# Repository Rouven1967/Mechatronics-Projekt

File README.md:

# Mechatronics-Projekt
Messtechnik für den Arbeitsschutz

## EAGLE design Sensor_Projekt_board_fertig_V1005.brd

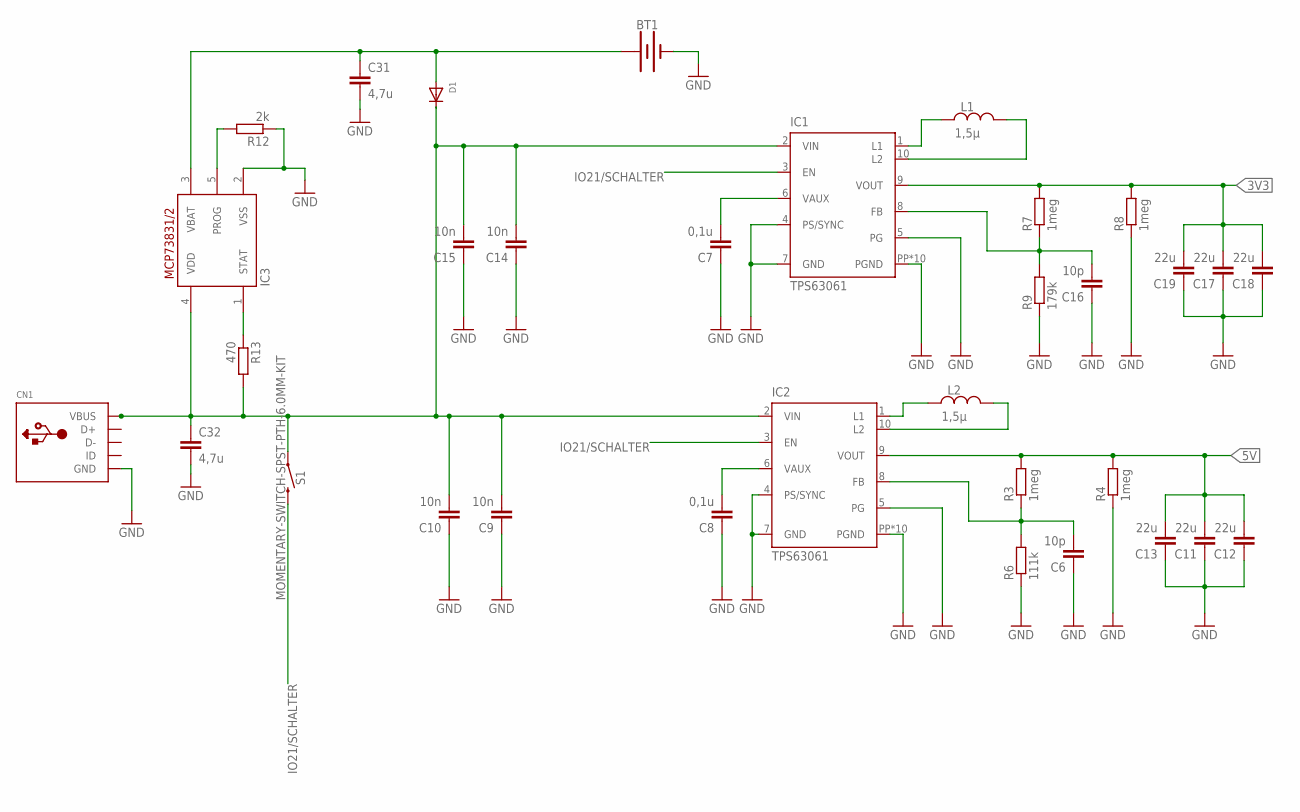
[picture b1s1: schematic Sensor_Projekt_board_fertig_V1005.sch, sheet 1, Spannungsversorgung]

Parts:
BT1: BATTERY-18650; BATTERY_18650-HOLDER
C6, C16: 10p; C0603
C7, C8: 0,1u; C0603
C9, C10, C14, C15: 10n; C0603
C11, C12, C13, C17, C18, C19: 22u; C0603
C31, C32: 4,7u; C0603
CN1: USBTHM; USB-MINIB-THM
D1: DIODE_SOD-123FL; SOD-123FL
IC1, IC2: TPS63061; DSC-S-PWSON-N10
IC3: MCP73831/OT; SOT23-5L
L1, L2: 1,5µ; INDC2520X120N
R3, R4, R7, R8: 1meg; R0603
R6: 111k; R0603
R9: 179k; R0603
R12: 2k; R0603
R13: 470; R0603
S1: MOMENTARY-SWITCH-SPST-PTH-6.0MM-KIT; TACTILE_SWITCH_PTH_6.0MM_KIT

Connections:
3V3: C17.2, C18.2, C19.2, IC1.9 (VOUT), R7.2, R8.2; also elsewhere on the board
5V: C11.2, C12.2, C13.2, IC2.9 (VOUT), R3.2, R4.2; also elsewhere on the board
GND: BT1.GND@1 (-), C6.1, C7.1, C8.1, C9.1, C10.1, C11.1, C12.1, C13.1, C14.1, C15.1, C16.1, C17.1, C18.1, C19.1, C31.2, C32.2, CN1.GND, IC1.4 (PS/SYNC), IC1.7 (GND), IC1.PP (PGND), IC1.PP@1 (PGND), IC1.PP@2 (PGND), IC1.PP@3 (PGND), IC1.PP@4 (PGND), IC1.PP@5 (PGND), IC1.PP@7 (PGND), IC1.PP@8 (PGND), IC1.PP@9 (PGND), IC1.PP@10 (PGND), IC2.4 (PS/SYNC), IC2.5 (PG), IC2.7 (GND), IC2.PP (PGND), IC2.PP@1 (PGND), IC2.PP@2 (PGND), IC2.PP@3 (PGND), IC2.PP@4 (PGND), IC2.PP@5 (PGND), IC2.PP@7 (PGND), IC2.PP@8 (PGND), IC2.PP@9 (PGND), IC2.PP@10 (PGND), IC3.2 (VSS), R4.1, R6.1, R8.1, R9.1, R12.1; also elsewhere on the board
IO21/SCHALTER: IC1.3 (EN), IC2.3 (EN), S1.3 (2); also elsewhere on the board
unnamed: IC3.5 (PROG), R12.2
unnamed: BT1.PWR@1 (+), C31.1, D1.A, IC3.3 (VBAT)
unnamed: C8.2, IC2.6 (VAUX)
unnamed: C7.2, IC1.6 (VAUX)
unnamed: C9.2, C10.2, C14.2, C15.2, C32.1, CN1.VBUS, D1.C, IC1.2 (VIN), IC2.2 (VIN), IC3.4 (VDD), R13.2, S1.1
unnamed: IC2.10 (L2), L2.2
unnamed: IC1.1 (L1), L1.1
unnamed: IC1.10 (L2), L1.2
unnamed: C6.2, IC2.8 (FB), R3.1, R6.2
unnamed: C16.2, IC1.8 (FB), R7.1, R9.2
unnamed: IC2.1 (L1), L2.1
unnamed: IC3.1 (STAT), R13.1

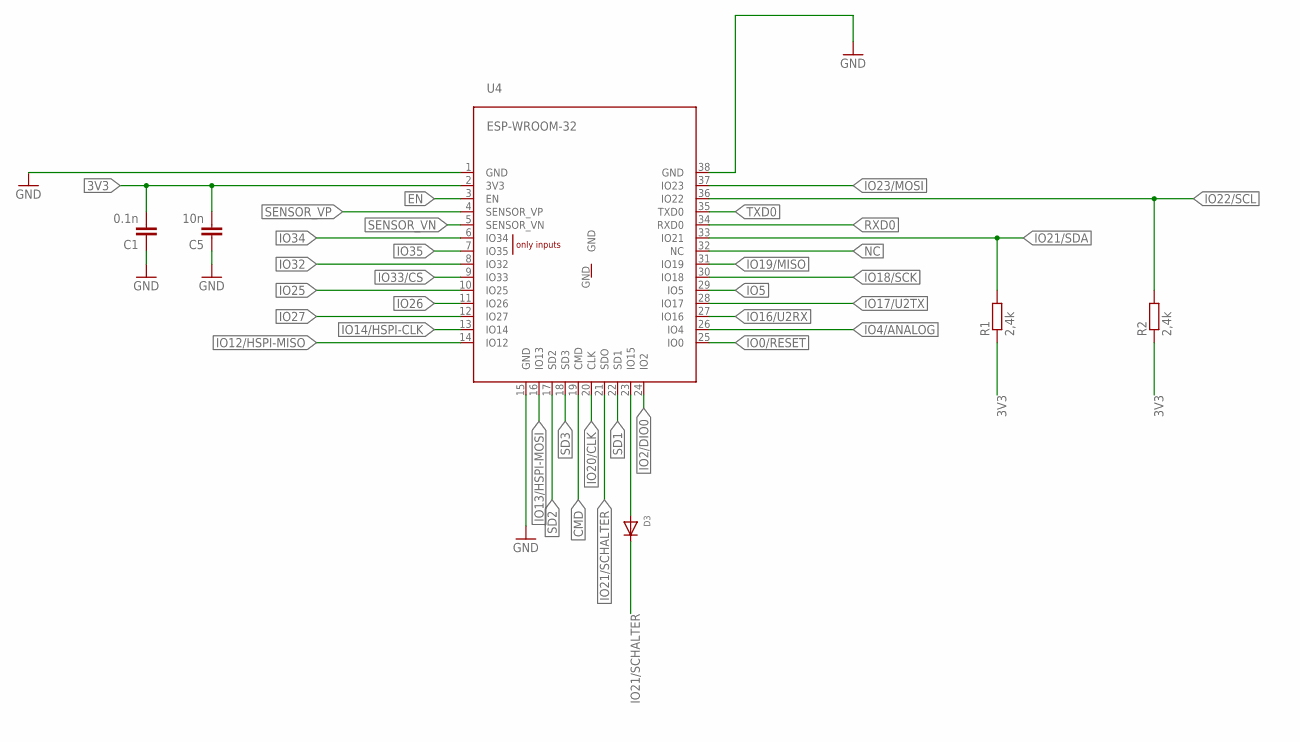
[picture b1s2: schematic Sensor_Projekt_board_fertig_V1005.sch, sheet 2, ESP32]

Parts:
C1: 0.1n; C0603
C5: 10n; C0603
D3: DIODE_SOD-123FL; SOD-123FL
R1, R2: 2,4k; R0603
U4: ESP-WROOM-32

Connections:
3V3: C1.2, C5.2, R1.1, R2.1, U4.2 (3V3); also elsewhere on the board
CMD: U4.19 (CMD)
EN: U4.3 (EN)
GND: C1.1, C5.1, U4.1 (GND), U4.15 (GND), U4.38 (GND); also elsewhere on the board
IO0/RESET: U4.25 (IO0); also elsewhere on the board
IO2/DIO0: U4.24 (IO2); also elsewhere on the board
IO4/ANALOG: U4.26 (IO4); also elsewhere on the board
IO5: U4.29 (IO5); also elsewhere on the board
IO12/HSPI-MISO: U4.14 (IO12); also elsewhere on the board
IO13/HSPI-MOSI: U4.16 (IO13); also elsewhere on the board
IO14/HSPI-CLK: U4.13 (IO14); also elsewhere on the board
IO15/VCC_ENABLE: D3.A, U4.23 (IO15)
IO16/U2RX: U4.27 (IO16); also elsewhere on the board
IO17/U2TX: U4.28 (IO17)
IO18/SCK: U4.30 (IO18); also elsewhere on the board
IO19/MISO: U4.31 (IO19); also elsewhere on the board
IO20/CLK: U4.20 (CLK)
IO21/SCHALTER: D3.C, U4.21 (SDO); also elsewhere on the board
IO21/SDA: R1.2, U4.33 (IO21); also elsewhere on the board
IO22/SCL: R2.2, U4.36 (IO22); also elsewhere on the board
IO23/MOSI: U4.37 (IO23); also elsewhere on the board
IO25: U4.10 (IO25)
IO26: U4.11 (IO26)
IO27: U4.12 (IO27)
IO32: U4.8 (IO32)
IO33/CS: U4.9 (IO33); also elsewhere on the board
IO34: U4.6 (IO34)
IO35: U4.7 (IO35)
NC: U4.32 (NC)
RXD0: U4.34 (RXD0); also elsewhere on the board
SD1: U4.22 (SD1)
SD2: U4.17 (SD2)
SD3: U4.18 (SD3)
SENSOR_VN: U4.5 (SENSOR_VN)
SENSOR_VP: U4.4 (SENSOR_VP)
TXD0: U4.35 (TXD0); also elsewhere on the board

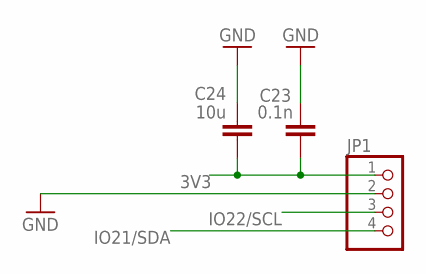
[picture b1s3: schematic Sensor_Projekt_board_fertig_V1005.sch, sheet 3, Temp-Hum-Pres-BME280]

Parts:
C23: 0.1n; C0603
C24: 10u; C0603
JP1: PINHD-1X4; 1X04

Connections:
3V3: C23.1, C24.1, JP1.1; also elsewhere on the board
GND: C23.2, C24.2, JP1.2; also elsewhere on the board
IO21/SDA: JP1.4; also elsewhere on the board
IO22/SCL: JP1.3; also elsewhere on the board

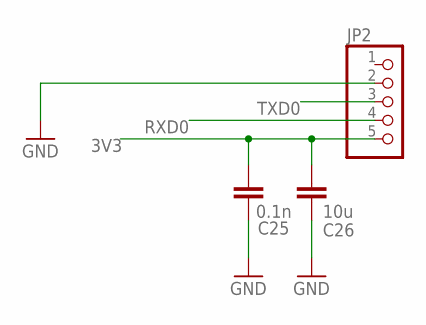
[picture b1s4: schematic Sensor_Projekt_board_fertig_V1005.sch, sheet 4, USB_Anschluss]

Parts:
C25: 0.1n; C0603
C26: 10u; C0603
JP2: PINHD-1X5; 1X05

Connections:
3V3: C25.1, C26.1, JP2.5; also elsewhere on the board
GND: C25.2, C26.2, JP2.2; also elsewhere on the board
RXD0: JP2.4; also elsewhere on the board
TXD0: JP2.3; also elsewhere on the board

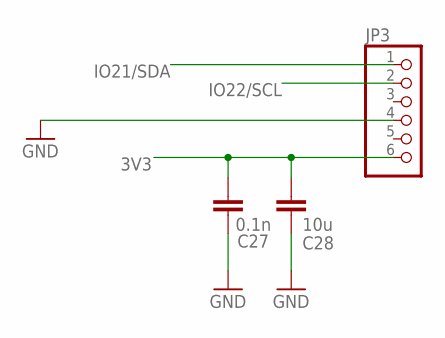
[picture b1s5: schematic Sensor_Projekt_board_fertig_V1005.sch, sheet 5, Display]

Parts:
C27: 0.1n; C0603
C28: 10u; C0603
JP3: PINHD-1X6; 1X06

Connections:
3V3: C27.1, C28.1, JP3.6; also elsewhere on the board
GND: C27.2, C28.2, JP3.4; also elsewhere on the board
IO21/SDA: JP3.1; also elsewhere on the board
IO22/SCL: JP3.2; also elsewhere on the board

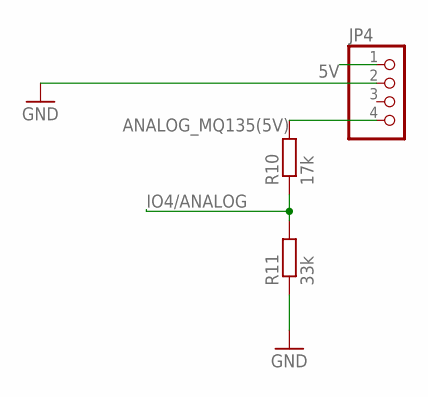
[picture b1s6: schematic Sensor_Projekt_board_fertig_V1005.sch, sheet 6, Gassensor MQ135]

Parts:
JP4: PINHD-1X4; 1X04
R10: 17k; R0603
R11: 33k; R0603

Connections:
5V: JP4.1; also elsewhere on the board
ANALOG_MQ135(5V): JP4.4, R10.2
GND: JP4.2, R11.1; also elsewhere on the board
IO4/ANALOG: R10.1, R11.2; also elsewhere on the board

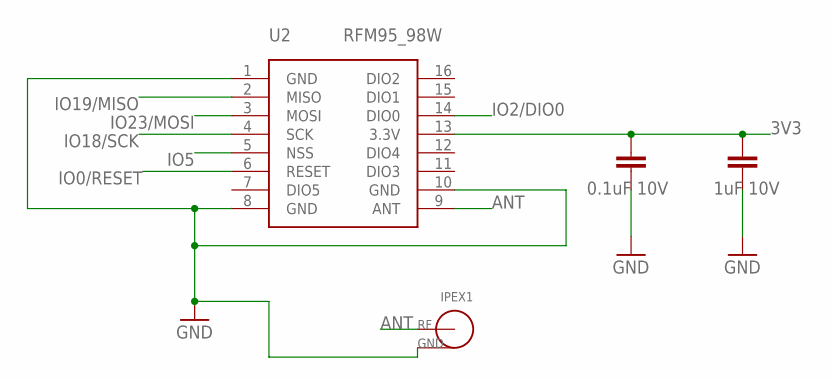
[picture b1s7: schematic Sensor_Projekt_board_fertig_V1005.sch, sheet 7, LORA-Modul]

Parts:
C4: 0.1uF 10V; C0402
C20: 1uF 10V; C0402
IPEX1: I-PEX
U2: RFM95_98W

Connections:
3V3: C4.2, C20.2, U2.13 (3.3V); also elsewhere on the board
ANT: IPEX1.SIG, U2.9 (ANT)
GND: C4.1, C20.1, IPEX1.GND, IPEX1.GND1 (GND), U2.1 (GND), U2.8 (GND), U2.10 (GND); also elsewhere on the board
IO0/RESET: U2.6 (RESET); also elsewhere on the board
IO2/DIO0: U2.14 (DIO0); also elsewhere on the board
IO5: U2.5 (NSS); also elsewhere on the board
IO18/SCK: U2.4 (SCK); also elsewhere on the board
IO19/MISO: U2.2 (MISO); also elsewhere on the board
IO23/MOSI: U2.3 (MOSI); also elsewhere on the board

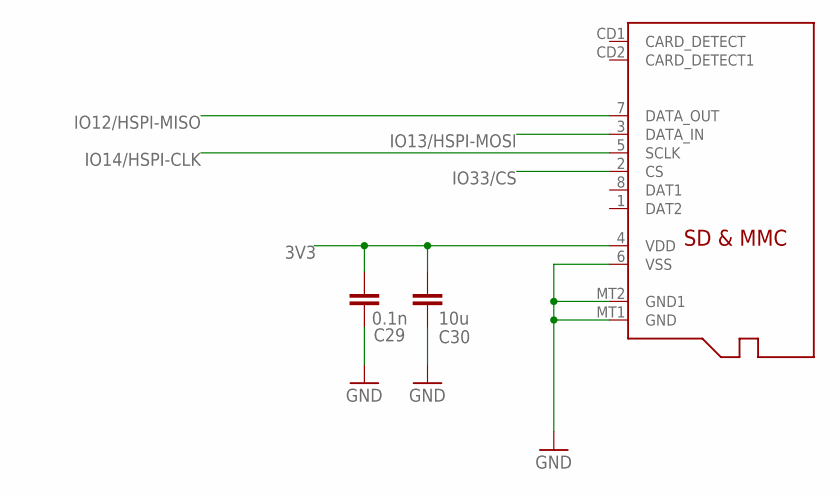
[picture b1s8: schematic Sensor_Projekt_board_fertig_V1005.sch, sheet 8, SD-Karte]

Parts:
C29: 0.1n; C0603
C30: 10u; C0603
U$16: MICROSD

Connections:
3V3: C29.1, C30.1, U$16.4 (VDD); also elsewhere on the board
GND: C29.2, C30.2, U$16.6 (VSS), U$16.MT1 (GND), U$16.MT2 (GND1); also elsewhere on the board
IO12/HSPI-MISO: U$16.7 (DATA_OUT); also elsewhere on the board
IO13/HSPI-MOSI: U$16.3 (DATA_IN); also elsewhere on the board
IO14/HSPI-CLK: U$16.5 (SCLK); also elsewhere on the board
IO33/CS: U$16.2 (CS); also elsewhere on the board

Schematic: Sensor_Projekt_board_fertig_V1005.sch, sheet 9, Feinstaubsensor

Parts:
C21: 10uF; 0805
C22: 0.1n; C0603
JP5: PINHD-1X8; 1X08

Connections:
5V: C21.2, C22.2, JP5.8; also elsewhere on the board
GND: C21.1, C22.1, JP5.7; also elsewhere on the board
IO16/U2RX: JP5.4; also elsewhere on the board
NC/IO17/U2TX: JP5.5
NG: JP5.1, JP5.2
RST: JP5.3
SET: JP5.6

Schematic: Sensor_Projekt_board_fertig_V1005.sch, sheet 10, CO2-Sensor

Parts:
JP6: PINHD-1X4; 1X04

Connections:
5V: JP6.1; also elsewhere on the board
GND: JP6.2; also elsewhere on the board
IO21/SDA: JP6.4; also elsewhere on the board
IO22/SCL: JP6.3; also elsewhere on the board

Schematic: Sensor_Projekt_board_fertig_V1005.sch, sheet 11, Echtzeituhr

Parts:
B1: cr1220; CR1220-2
C2, C3: 10uF; 0805
INT1: HEADER-1X1ROUND; 1X01_ROUND
Q1: FC-12M
R5: 1k; R0603
U7: PCF8523T; SOT96-1

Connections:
3V3: C3.2, R5.1; also elsewhere on the board
GND: B1.-, C2.1, C3.1, U7.4 (VSS); also elsewhere on the board
IO21/SDA: U7.5 (SDA); also elsewhere on the board
IO22/SCL: U7.6 (SCL); also elsewhere on the board
unnamed: INT1.1, U7.7 (!INT1)
unnamed: Q1.1, U7.1 (OSCI)
unnamed: Q1.2, U7.2 (OSCO)
unnamed: B1.+, U7.3 (VBAT)
unnamed: C2.2, R5.2, U7.8 (VDD)

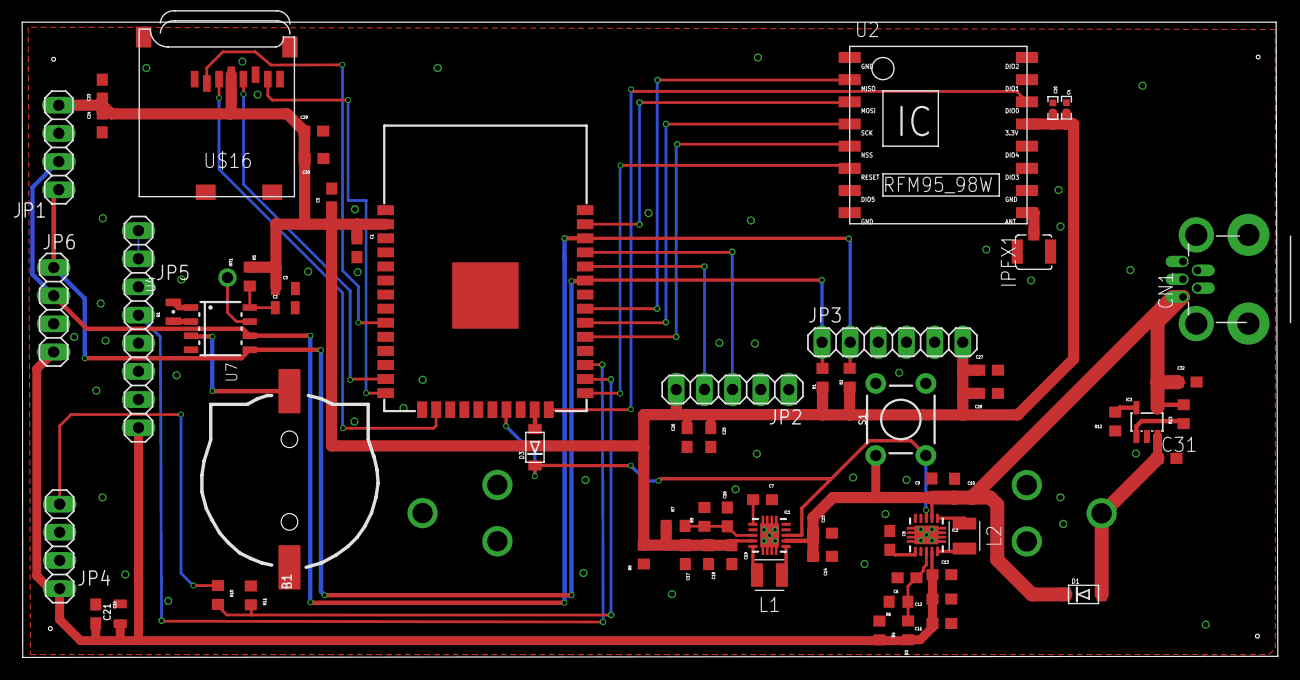
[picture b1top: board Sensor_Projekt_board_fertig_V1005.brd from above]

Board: 2 copper layers, 113.3 x 57.3 mm, 69 parts (1 on the bottom side), 41 nets.

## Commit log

2020-04-30 Add files via upload
    test
2020-06-18 optimized version V3
2020-06-18 First board version V3
2020-06-18 optimized version V4
2020-06-18 optimized version V5
2020-06-18 First version V3

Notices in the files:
parts and their libraries:
SparkFun-Capacitors: Licensing: Creative Commons ShareAlike 4.0 International - https://creativecommons.org/licenses/by-sa/4.0
NXP_60_26022015: This library may be distributed and adapted freely for any purpose, as long as NXP is credited and any new creation is licensed under the same terms.
